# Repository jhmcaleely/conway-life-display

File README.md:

# conway-life-display

Conway's Life implemented on a LED cube, hosted on a Raspberry Pi Pico.

Some [reverse engineered notes](docs/cube-bit.md) of the [4tronix LED Cube](https://shop.4tronix.co.uk/products/cubebit).

Implemented in C and Micropython. Either implementation can be run as firmware on the Pico.

## Hardware

`cube-bit/`

contains a kicad project that connects a pico to the 40-pin Pi connector.

`Plinth/`

contains a lightburn project to create a plinth for the Cube:Bit + Pico to sit on. Originally drawn using [Boxes.py](https://boxes.hackerspace-bamberg.de/?language=en).

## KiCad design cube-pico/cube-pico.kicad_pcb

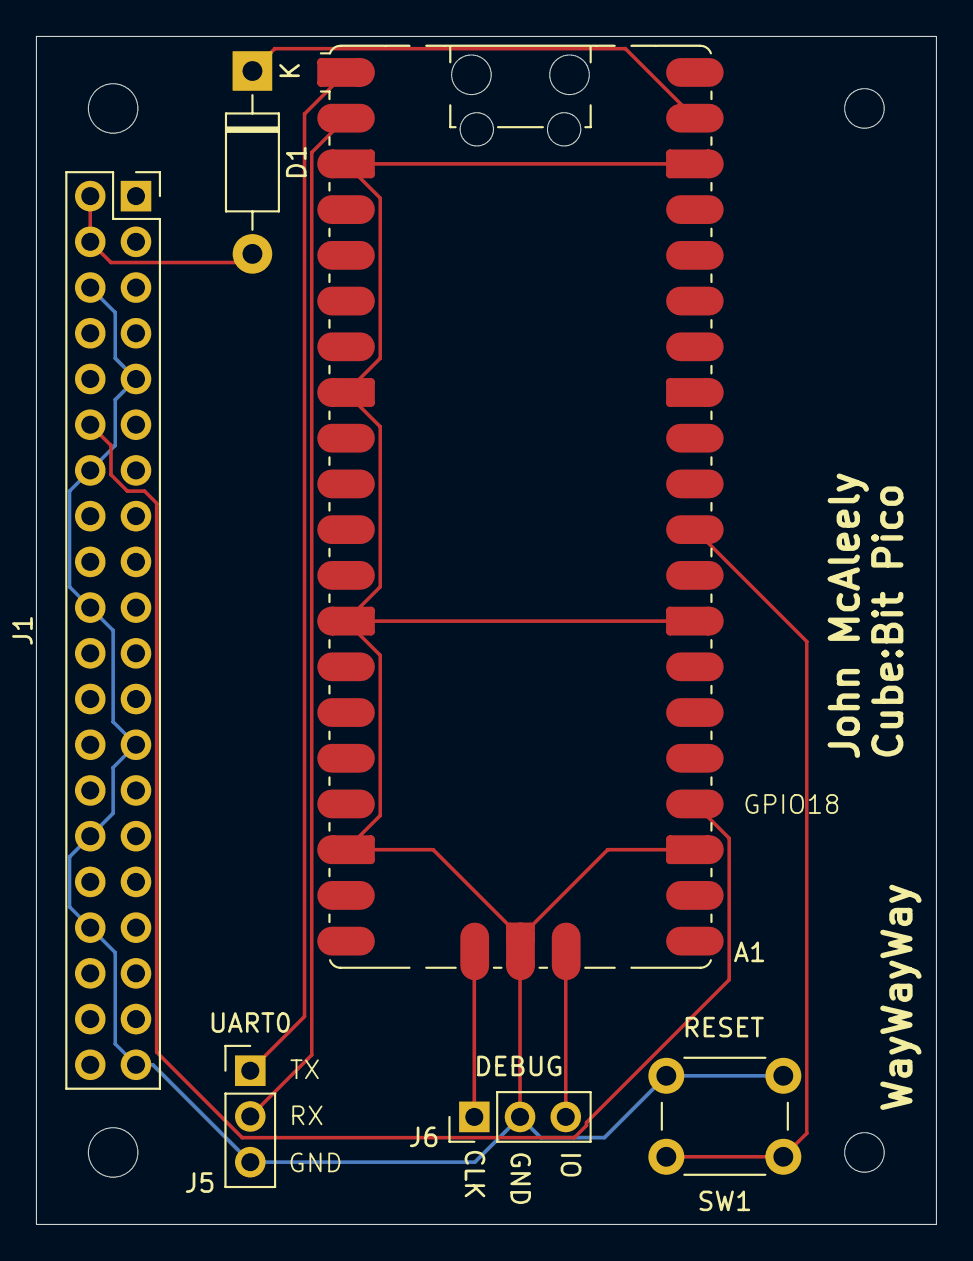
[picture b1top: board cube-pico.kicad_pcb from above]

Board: 2 copper layers, 50.0 x 66.0 mm, 6 parts (0 on the bottom side), 10 nets.

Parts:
A1: RaspberryPi_Pico; RaspberryPi_Pico_SMD_HandSolder
D1: 1N5817; D_DO-41_SOD81_P10.16mm_Horizontal
J1: Raspberry_Pi_4; Raspberry_Pi_Zero_Socketed_THT_FaceDown_MountingHoles
J5: UART0; PinHeader_1x03_P2.54mm_Vertical
J6: DEBUG; PinHeader_1x03_P2.54mm_Vertical
SW1: RESET; SW_PUSH_6mm

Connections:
GND: A1.3 (GND), A1.8 (GND), A1.13 (GND), A1.18 (GND), A1.23 (GND), A1.28 (GND), A1.38 (GND), A1.D2 (GND), J1.6 (GND), J1.9 (GND), J1.14 (GND), J1.20 (GND), J1.25 (GND), J1.30 (GND), J1.34 (GND), J1.39 (GND), J5.3, J6.2 (GND), SW1.1
unnamed: A1.1 (GPIO0), J5.1
unnamed: A1.2 (GPIO1), J5.2
unnamed: A1.24 (GPIO18), J1.12 (GPIO18/SPI1_~CE0/PCM_CLK/PWM0)
unnamed: A1.30 (RUN), SW1.2
unnamed: A1.D1 (SWCLK), J6.1 (SWCLK)
unnamed: A1.D3 (SWDIO), J6.3 (SWDIO)
unnamed: A1.39 (VSYS), D1.1 (K)
unnamed: D1.2 (A), J1.2 (5V), J1.4 (5V)
unnamed: J1.1 (3V3), J1.17 (3V3)

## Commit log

2022-05-28 Project brief added to readme
2022-05-28 Placeholder for a Python implementation
2022-05-28 some scratchy thoughts
2022-05-29 add some display routines
2022-05-29 some sketchy implementation
2022-05-29 it's alive: first iterations that seem to work
2022-05-29 now with correct map lifetime
2022-05-29 remove unused function
2022-05-29 minor updates
2022-05-29 idomatic refactoring
2022-05-29 prefer 'world' instead of 'map'
2022-06-03 copy of cubebit.py from https://github.com/jhmcaleely/cube-bit @ e0be57a
2022-06-03 a place to show the life world on an LED cube
2022-06-03 first display on the cube!
2022-06-03 some tidying up
2024-07-15 initial port to pico:ed
2024-07-15 port display-life to pico:ed
2024-07-15 run two life matrixes
2024-07-15 remove redundant files
2024-07-15 remove old test code
2024-07-16 tidying up
2024-07-16 move LED cube to separate file
2024-07-16 add readme
2024-07-16 Initial implementation
    Initial implementation
2025-03-31 move micropython implementation
2025-03-31 Initial C demo code from pico samples. Drives bottom plane of 4x4 cube:bit.
2025-03-31 Enable all 64 LEDs, and arbitrarily clamp brightness to half (require 2.5A USB power supply)
2025-03-31 Add SDK Licence notice for ws2812 example
2025-03-31 Move to GPIO18, so GPIO on pico matches 40-pin Pi header
2025-03-31 remove unwanted ws2812_parallel
2025-03-31 drop to 48MHz clock for pico
2025-03-31 set up cube_life target, modify pio to be 24bit only.
2025-03-31 define pixels, and define how they are written to the cube's data line.
2025-03-31 clearer computation of pixel max and divisor
2025-03-31 Improved documentation
2025-03-31 Formating for README
    Add more info on Cube:Bit
2025-03-31 remove redundant .vscode from .gitignore
2025-04-01 An initial prototype
2025-04-01 Micropython on the Pico
2025-04-01 tidying, add clamping, move toward same algorithms in c and micropython
2025-04-01 refactoring to separate out cube_bit
2025-04-01 fix neighbour_of and align names with python
2025-04-01 align names and algoirithms
2025-04-01 reorder declarations
2025-04-01 refactor for closer alignment
2025-04-01 remove unsued parameter
2025-04-01 fix transcription bug
2025-04-01 Update README.md to remove pico:ed references
2025-04-01 Add callbacks for neighbours, and better names for surface leds
2025-04-01 clearer whitespace
2025-04-01 name consistency
2025-04-13 initial hardware design
2025-04-13 documentation update
2025-04-24 add laser cut plinth
2025-04-24 Some documentation updates, and tidy up Plinth
2025-04-24 Docs update. Add a photo
2025-04-24 fix broken link
2025-04-24 Doc clarification
2025-05-02 Add power supply notes
